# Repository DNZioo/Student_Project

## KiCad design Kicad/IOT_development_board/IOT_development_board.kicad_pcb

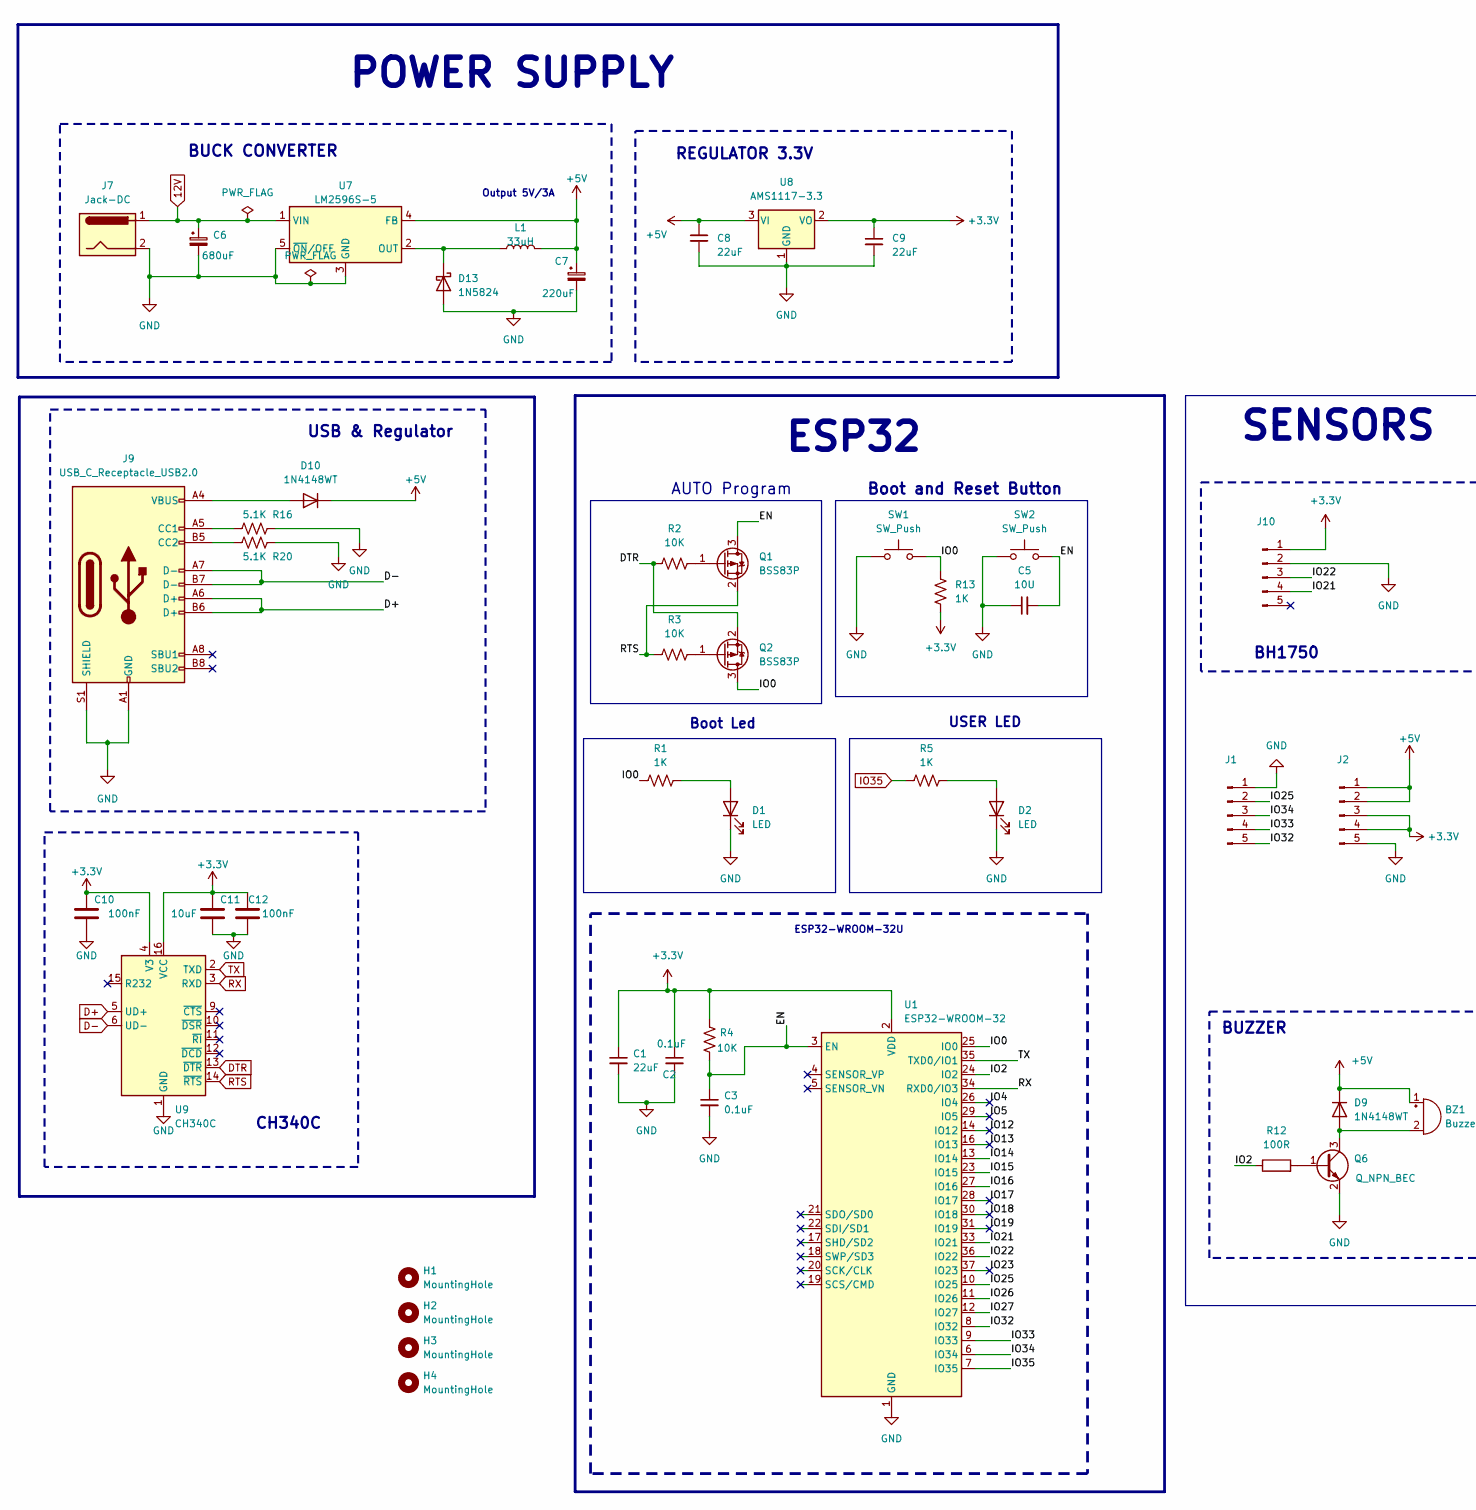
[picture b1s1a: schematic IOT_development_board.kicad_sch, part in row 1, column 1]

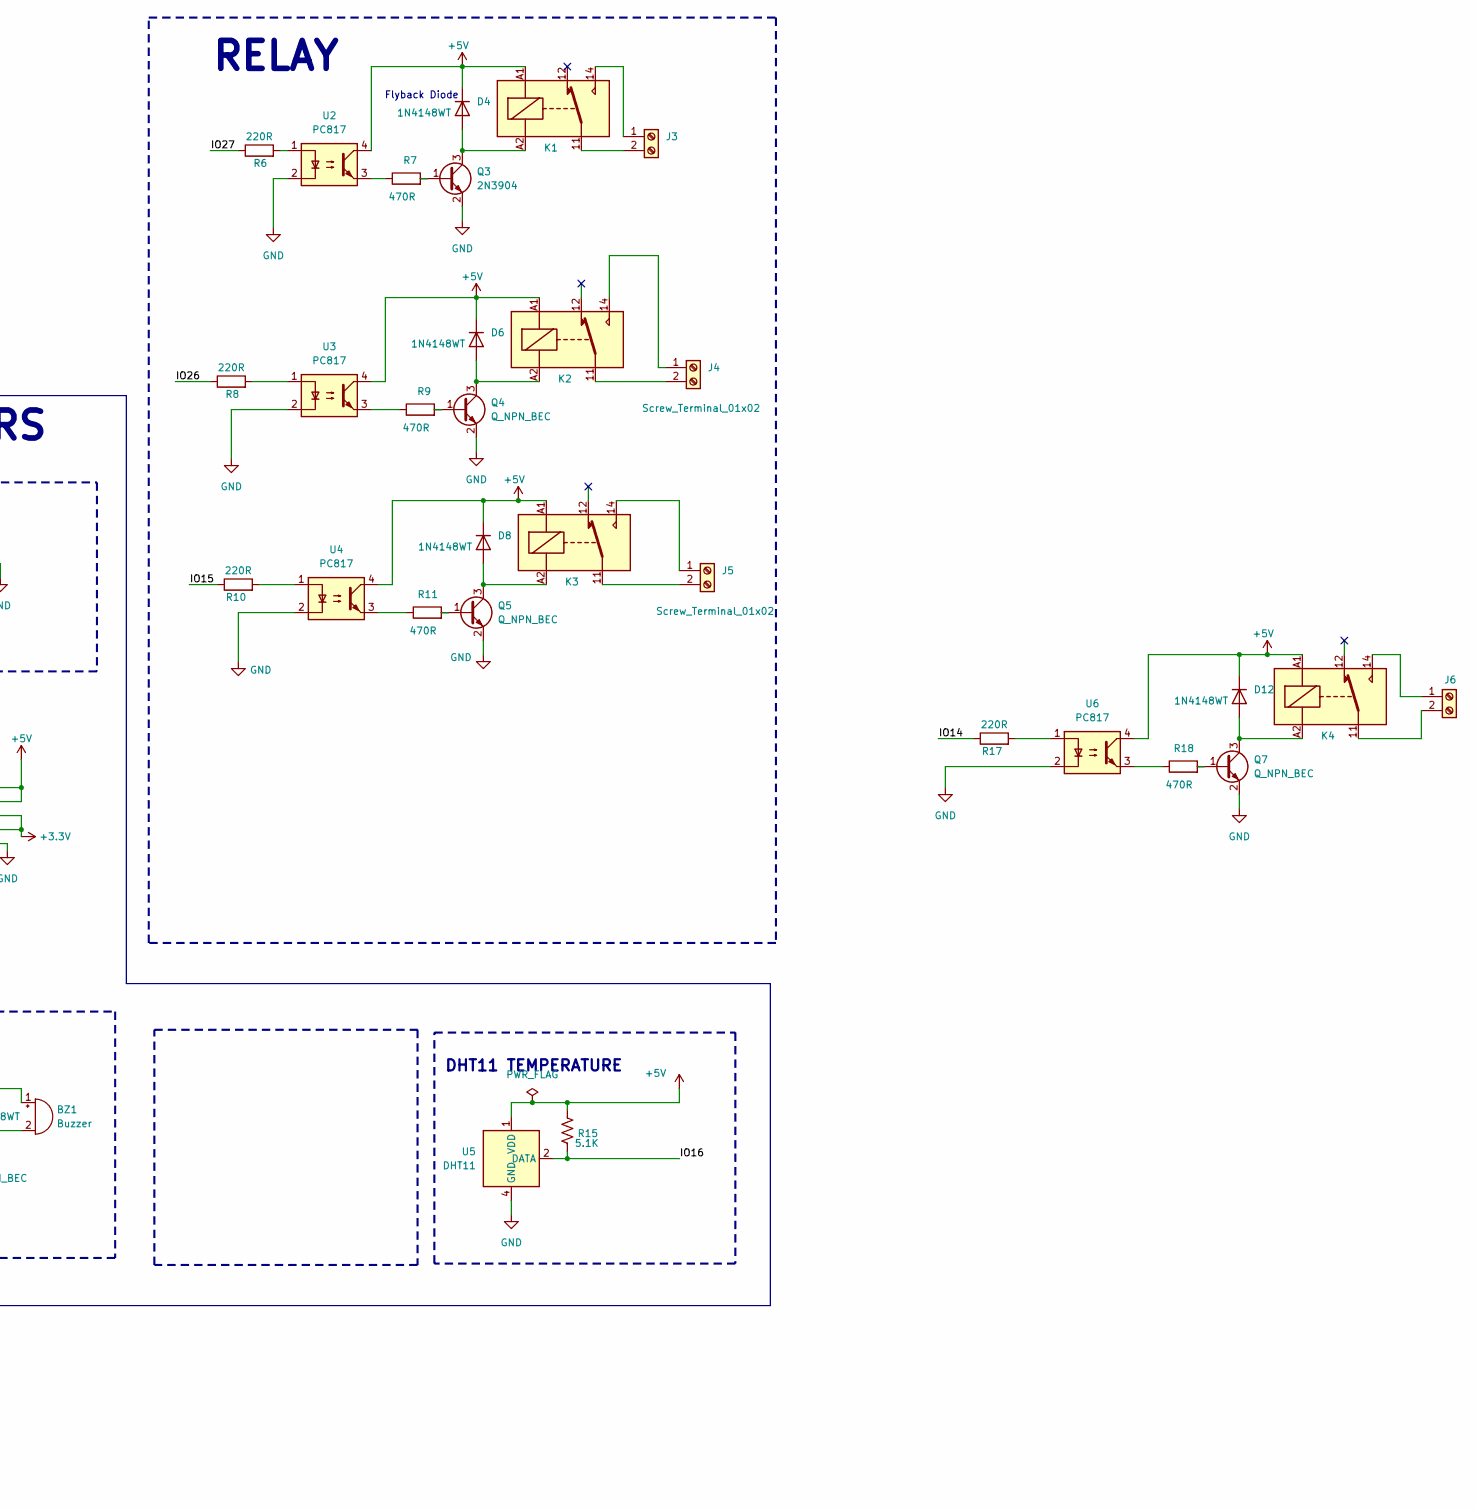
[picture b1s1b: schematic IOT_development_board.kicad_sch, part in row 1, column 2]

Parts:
BZ1: Buzzer; Buzzer_TDK_PS1240P02BT_D12.2mm_H6.5mm
C1, C8, C9: 22uF; C_0603_1608Metric
C2, C3: 0.1uF; C_0603_1608Metric
C5: 10U; C_0603_1608Metric
C6: 680uF; CP_Elec_6.3x9.9
C7: 220uF; CP_Elec_6.3x9.9
C10, C12: 100nF; C_0603_1608Metric
C11: 10uF; C_0603_1608Metric
D1, D2: LED; LED_0603_1608Metric
D4, D6, D8, D12: 1N4148WT; D_SOD-523
D9, D10: 1N4148WT; D_SOD-123
D13: 1N5824; D_SOD-128
H1, H2, H3, H4: MountingHole; MountingHole_3.2mm_M3_Pad_Via
J1, J2, J10: Conn_01x05_Pin; PinHeader_1x05_P2.54mm_Vertical
J3, J4, J5, J6: Screw_Terminal_01x02; TerminalBlock_Phoenix_MKDS-1,5-2-5.08_1x02_P5.08mm_Horizont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
J7: Jack-DC; BarrelJack_Horizontal
J9: USB_C_Receptacle_USB2.0; USB_C_Receptacle_HRO_TYPE-C-31-M-12
K1, K2, K3, K4: Fujitsu_FTR-LYCA005x; Relay_SPDT_SANYOU_SRD_Series_Form_C_1
L1: 33uH; L_7.3x7.3_H3.5
Q1, Q2: BSS83P; SOT-23
Q3: 2N3904; SOT-23-3
Q4, Q5, Q6, Q7: Q_NPN_BEC; SOT-23-3
R1, R5, R13: 1K; R_0603_1608Metric
R2, R3, R4: 10K; R_0603_1608Metric
R6, R8, R10, R17: 220R; R_0603_1608Metric
R7, R9, R11, R18: 470R; R_0603_1608Metric
R12: 100R; R_0603_1608Metric
R15, R16, R20: 5.1K; R_0603_1608Metric
SW1, SW2: SW_Push; SW_SPST_B3U-1000P
U1: ESP32-WROOM-32
U2, U3, U4, U6: PC817
U5: DHT11; Aosong_DHT11_5.5x12.0_P2.54mm
U7: LM2596S-5; TO-263-5_TabPin3
U8: AMS1117-3.3; SOT-89-3
U9: CH340C; SOIC-16_3.9x9.9mm_P1.27mm

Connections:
12V: C6.1, J7.1, U7.1 (VIN)
+3.3V: C1.1, C2.1, C9.1, C10.1, C11.1, C12.1, J2.3, J2.4, J10.1, R4.1, R13.1, U1.2 (VDD), U8.2 (VO), U9.4 (V3), U9.16 (VCC); also elsewhere on the board
+5V: BZ1.1 (+), C7.1, C8.1, D4.1 (K), D6.1 (K), D8.1 (K), D9.1 (K), D10.1 (K), D12.1 (K), J2.1, J2.2, K1.A1, K2.A1, K3.A1, K4.A1, L1.2, R15.1, U2.4, U3.4, U4.4, U5.1 (VDD), U6.4, U7.4 (FB), U8.3 (VI)
/EN: C3.1, C5.2, Q1.3 (D), R4.2, SW2.2, U1.3 (EN)
/IO0: Q2.3 (D), R1.1, R13.2, SW1.2, U1.25 (IO0)
/IO2: R12.1, U1.24 (IO2)
/IO4: U1.26 (IO4)
/IO5: U1.29 (IO5)
/IO12: U1.14 (IO12)
/IO13: U1.16 (IO13)
/IO14: R17.1, U1.13 (IO14)
/IO15: R10.1, U1.23 (IO15)
/IO16: R15.2, U1.27 (IO16), U5.2 (DATA)
/IO17: U1.28 (IO17)
/IO18: U1.30 (IO18)
/IO19: U1.31 (IO19)
/IO21: J10.4, U1.33 (IO21)
/IO22: J10.3, U1.36 (IO22)
/IO23: U1.37 (IO23)
/IO25: J1.2, U1.10 (IO25)
/IO26: R8.1, U1.11 (IO26)
/IO27: R6.1, U1.12 (IO27)
/IO32: J1.5, U1.8 (IO32)
/IO33: J1.4, U1.9 (IO33)
/IO34: J1.3, U1.6 (IO34)
D+: J9.A6 (D+), J9.B6 (D+), U9.5 (UD+)
D-: J9.A7 (D-), J9.B7 (D-), U9.6 (UD-)
DTR: Q2.2 (S), R2.1, U9.13 (~DTR)
GND: C1.2, C2.2, C3.2, C5.1, C6.2, C7.2, C8.2, C9.2, C10.2, C11.2, C12.2, D1.1 (K), D2.1 (K), D13.2 (A), J1.1, J2.5, J7.2, J9.A1 (GND), J9.A12 (GND), J9.B1 (GND), J9.B12 (GND), J9.S1 (SHIELD), J10.2, Q3.2 (E), Q4.2 (E), Q5.2 (E), Q6.2 (E), Q7.2 (E), R16.2, R20.2, SW1.1, SW2.1, U1.1 (GND), U1.15 (GND), U1.38 (GND), U1.39 (GND), U2.2, U3.2, U4.2, U5.4 (GND), U6.2, U7.3 (GND), U7.5 (~ON/OFF), U8.1 (GND), U9.1 (GND); also elsewhere on the board
IO35: R5.1, U1.7 (IO35)
unnamed: BZ1.2 (-), D9.2 (A), Q6.3 (C)
unnamed: D1.2 (A), R1.2
unnamed: D2.2 (A), R5.2
unnamed: D4.2 (A), K1.A2, Q3.3 (C)
unnamed: D6.2 (A), K2.A2, Q4.3 (C)
unnamed: D8.2 (A), K3.A2, Q5.3 (C)
unnamed: D10.2 (A), J9.A4 (VBUS), J9.A9 (VBUS), J9.B4 (VBUS), J9.B9 (VBUS)
unnamed: D12.2 (A), K4.A2, Q7.3 (C)
unnamed: D13.1 (K), L1.1, U7.2 (OUT)
unnamed: J3.1, K1.14
unnamed: J3.2, K1.11
unnamed: J4.1, K2.14
unnamed: J4.2, K2.11
unnamed: J5.1, K3.14
unnamed: J5.2, K3.11
unnamed: J6.1, K4.14
unnamed: J6.2, K4.11
unnamed: J9.A5 (CC1), R16.1
unnamed: J9.B5 (CC2), R20.1
unnamed: Q1.1 (G), R2.2
unnamed: Q2.1 (G), R3.2
unnamed: Q3.1 (B), R7.2
unnamed: Q4.1 (B), R9.2
unnamed: Q5.1 (B), R11.2
unnamed: Q6.1 (B), R12.2
unnamed: Q7.1 (B), R18.2
unnamed: R6.2, U2.1
unnamed: R7.1, U2.3
unnamed: R8.2, U3.1
unnamed: R9.1, U3.3
unnamed: R10.2, U4.1
unnamed: R11.1, U4.3
unnamed: R17.2, U6.1
unnamed: R18.1, U6.3
RTS: Q1.2 (S), R3.1, U9.14 (~RTS)
RX: U1.34 (RXD0/IO3), U9.3 (RXD)
TX: U1.35 (TXD0/IO1), U9.2 (TXD)

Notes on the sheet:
Flyback Diode
Boot and Reset Button
Output 5V/3A
BUCK CONVERTER
USB & Regulator
ESP32-WROOM-32U
RELAY
CH340C
DHT11 TEMPERATURE
AUTO Program
POWER SUPPLY
REGULATOR 3.3V
Boot Led
ESP32
BH1750
BUZZER
SENSORS
USER LED

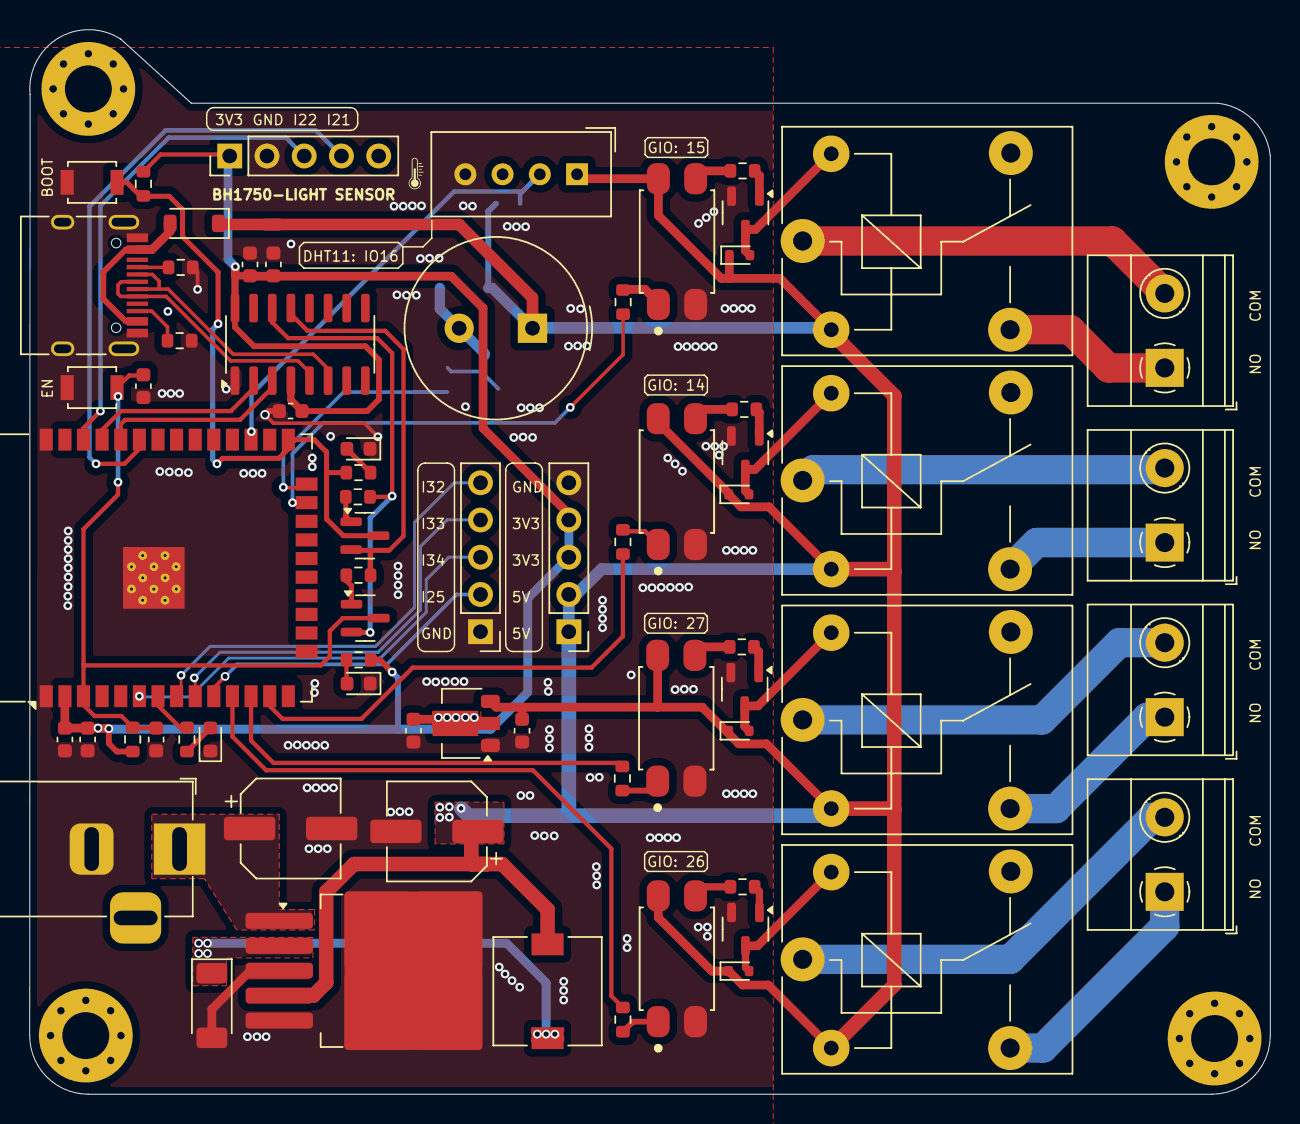
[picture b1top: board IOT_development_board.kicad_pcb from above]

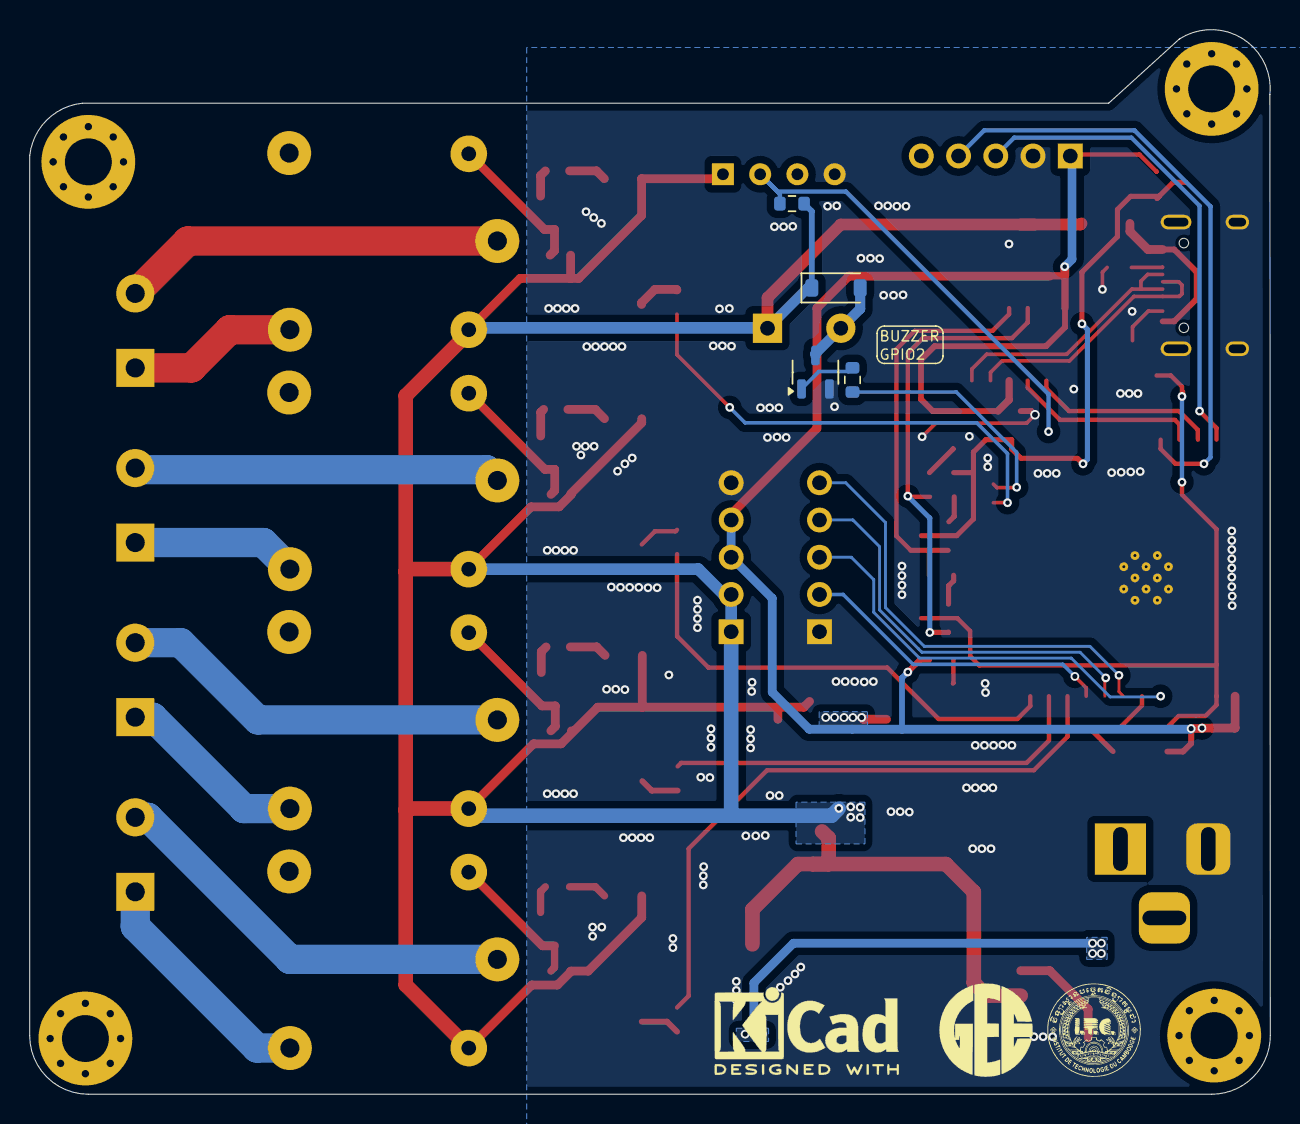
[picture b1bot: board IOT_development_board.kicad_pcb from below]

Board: 2 copper layers, 84.6 x 72.6 mm, 77 parts (4 on the bottom side), 60 nets.

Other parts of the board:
D14: LED; LED_0603_1608Metric
R19: 220; R_0603_1608Metric

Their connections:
+3.3V: R19.1; also elsewhere on the board
GND: D14.1 (K); also elsewhere on the board
unnamed: D14.2 (A), R19.2

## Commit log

2024-12-04 test
2024-12-11 testing get data
